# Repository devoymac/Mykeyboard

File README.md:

# Mykeyboard — Split Ergo Keyboard

Teclado ergonómico split de diseño propio. Proyecto de hardware abierto: esquemáticos y PCB en KiCad, firmware en QMK, y carcasa imprimible en 3D.

## Layout

Split columnar-stagger ISO-ES (español completo: Ñ, Ç, ‡, ¡, ¿), ~38 teclas por mitad, espacio dividido y flechas dedicadas.

## Estado

En desarrollo. Estructura del proyecto montada, KiCad 10.0.6 instalado, requisitos y layout definidos.

## Estructura del proyecto

```
Mykeyboard/
├── hardware/          # Diseño electrónico (KiCad)
│   ├── left/          # Mitad izquierda (esquemático + PCB)
│   ├── right/         # Mitad derecha (espejo de la izquierda)
│   └── shared/        # Librerías, símbolos, footprints y plantillas comunes
├── firmware/          # Firmware del teclado (QMK)
├── case/              # Carcasa imprimible en 3D (STL / FreeCAD)
├── docs/              # Documentación: requisitos, layout, BOM, decisiones
├── tools/             # Scripts de utilidad (generación, automatización)
└── README.md
```

## Hardware

- **KiCad**: 10.0.6 (esquemático y PCB).
- **Layout**: split columnar-stagger ISO-ES, ~37-38 teclas por mitad, placa única que se parte en dos (V-cut/mouse bites).
- **Controlador**: RP2040-Zero por mitad, conectadas por TRRS.
- **Switches**: Outemu Silent Lemon V3 (táctiles silenciosos), soldados.
- **Pantalla**: OLED 128x32 (I2C) en la mitad izquierda.
- **Extras**: encoder rotatorio EC11 (volumen/medios) en la mitad derecha.
- Ver [docs/requirements.md](docs/requirements.md), [docs/layout.md](docs/layout.md) y el [BOM](docs/bom.md).

## Firmware

QMK (cableado).

## Cómo contribuir / desarrollo

1. Clona el repositorio.
2. Abre los proyectos de KiCad en `hardware/left` y `hardware/right`.
3. Documenta cualquier cambio relevante en `docs/`.

## Licencia

Pendiente de decidir (recomendado: CERN-OHL-S para hardware, MIT para firmware).

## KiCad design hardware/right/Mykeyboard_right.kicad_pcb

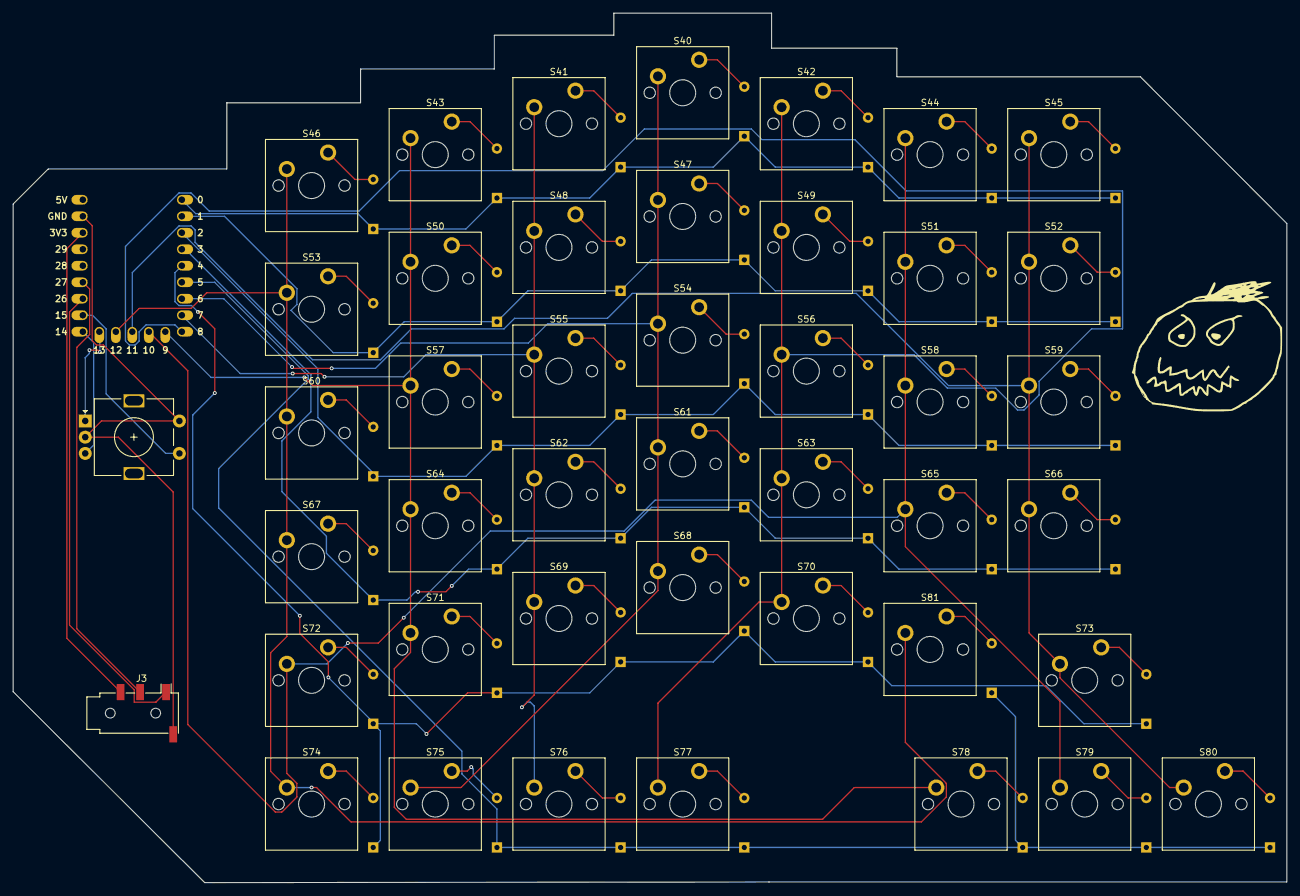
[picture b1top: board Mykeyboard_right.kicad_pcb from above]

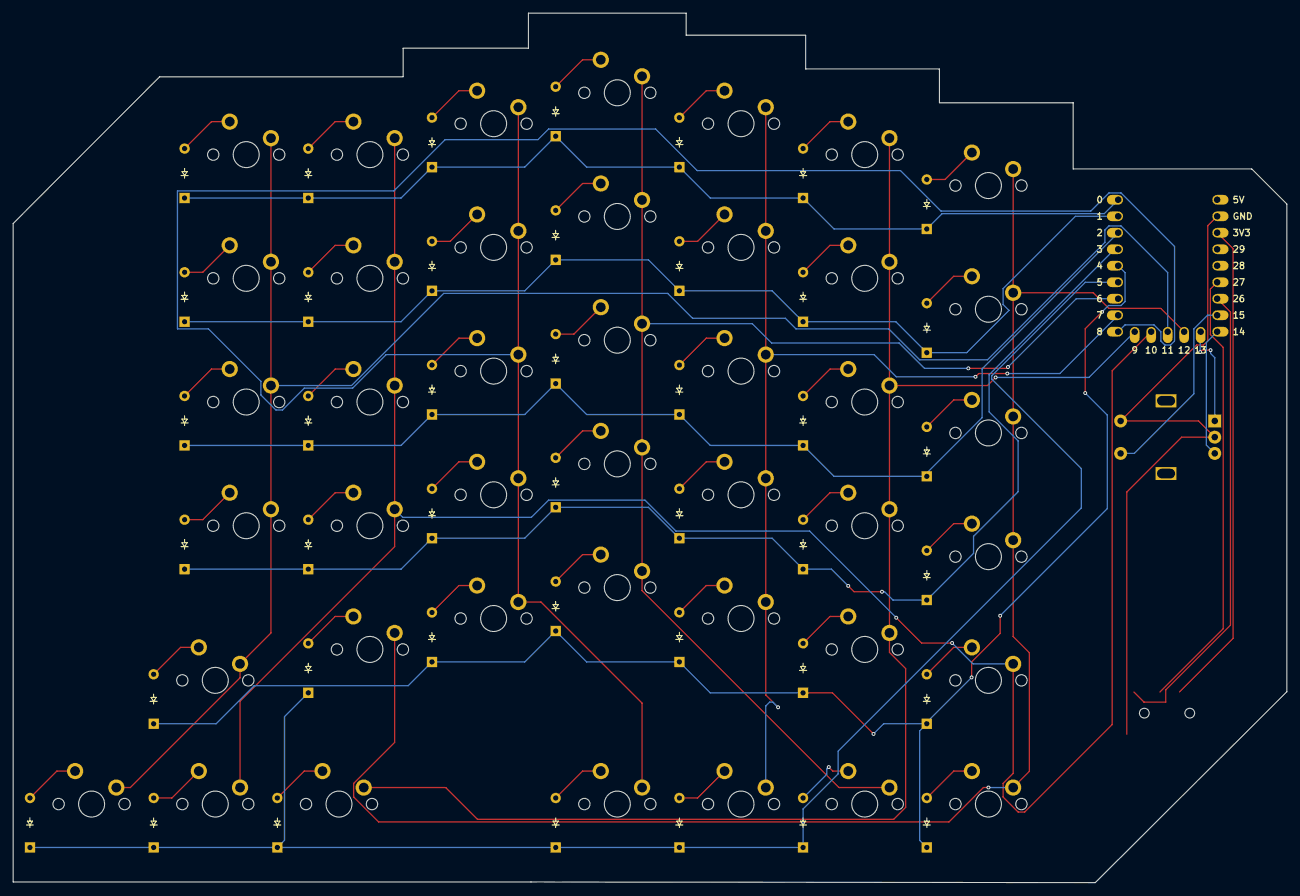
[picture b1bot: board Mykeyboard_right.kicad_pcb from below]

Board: 2 copper layers, 196.1 x 133.9 mm, 87 parts (42 on the bottom side), 62 nets.

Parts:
D40, D41, D42, D43, D44, D45, D46, D47, D48, D49, D50, D51, D52, D53, D54, D55, D56, D57, D58, D59, D60, D61, D62, D63, D64, D65, D66, D67, D68, D69, D70, D71, D72, D73, D74, D75, D76, D77, D78, D79, D80, D81: Diode_DO-35
J3: AudioJack4; Jack_3.5mm_PJ320D_Horizontal
S40, S41, S42, S43, S44, S45, S46, S47, S48, S49, S50, S51, S52, S53, S54, S55, S56, S57, S58, S59, S60, S61, S62, S63, S64, S65, S66, S67, S68, S69, S70, S71, S72, S73, S74, S75, S76, S77, S78, S79, S80, S81: MX_PCB_1.00u
SW1: RotaryEncoder_Switch; RotaryEncoder_Alps_EC11E-Switch_Vertical_H20mm
U2: RP2040_Zero

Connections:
/colum 7: S40.1, S47.1, S54.1, S61.1, S68.1, S75.1, U2.7 (6)
/colum 8: S41.1, S48.1, S55.1, S62.1, S69.1, S76.1, U2.8 (7)
/colum 9: S42.1, S49.1, S56.1, S63.1, S70.1, S77.1, U2.9 (8)
/colum 10: S43.1, S50.1, S57.1, S64.1, S71.1, S78.1, U2.10 (9)
/colum 11: S44.1, S51.1, S58.1, S65.1, S72.1, S79.1, U2.11 (10)
/colum 12: S45.1, S52.1, S59.1, S66.1, S73.1, S80.1, U2.12 (11)
/colum 13: S46.1, S53.1, S60.1, S67.1, S74.1, S81.1, U2.13 (12)
/row 6: D40.1 (K), D41.1 (K), D42.1 (K), D43.1 (K), D44.1 (K), D45.1 (K), D46.1 (K), U2.1 (0)
/row 7: D47.1 (K), D48.1 (K), D49.1 (K), D50.1 (K), D51.1 (K), D52.1 (K), D53.1 (K), U2.2 (1)
/row 8: D54.1 (K), D55.1 (K), D56.1 (K), D57.1 (K), D58.1 (K), D59.1 (K), D60.1 (K), U2.3 (2)
/row 9: D61.1 (K), D62.1 (K), D63.1 (K), D64.1 (K), D65.1 (K), D66.1 (K), D67.1 (K), U2.4 (3)
/row 10: D68.1 (K), D69.1 (K), D70.1 (K), D71.1 (K), D72.1 (K), D73.1 (K), D74.1 (K), U2.5 (4)
/row 11: D75.1 (K), D76.1 (K), D77.1 (K), D78.1 (K), D79.1 (K), D80.1 (K), D81.1 (K), U2.6 (5)
unnamed: D40.2 (A), S40.2
unnamed: D41.2 (A), S41.2
unnamed: D42.2 (A), S42.2
unnamed: D43.2 (A), S43.2
unnamed: D44.2 (A), S44.2
unnamed: D45.2 (A), S45.2
unnamed: D46.2 (A), S46.2
unnamed: D47.2 (A), S47.2
unnamed: D48.2 (A), S48.2
unnamed: D49.2 (A), S49.2
unnamed: D50.2 (A), S50.2
unnamed: D51.2 (A), S51.2
unnamed: D52.2 (A), S52.2
unnamed: D53.2 (A), S53.2
unnamed: D54.2 (A), S54.2
unnamed: D55.2 (A), S55.2
unnamed: D56.2 (A), S56.2
unnamed: D57.2 (A), S57.2
unnamed: D58.2 (A), S58.2
unnamed: D59.2 (A), S59.2
unnamed: D60.2 (A), S60.2
unnamed: D61.2 (A), S61.2
unnamed: D62.2 (A), S62.2
unnamed: D63.2 (A), S63.2
unnamed: D64.2 (A), S64.2
unnamed: D65.2 (A), S65.2
unnamed: D66.2 (A), S66.2
unnamed: D67.2 (A), S67.2
unnamed: D68.2 (A), S68.2
unnamed: D69.2 (A), S69.2
unnamed: D70.2 (A), S70.2
unnamed: D71.2 (A), S71.2
unnamed: D72.2 (A), S72.2
unnamed: D73.2 (A), S73.2
unnamed: D74.2 (A), S74.2
unnamed: D75.2 (A), S75.2
unnamed: D76.2 (A), S76.2
unnamed: D77.2 (A), S77.2
unnamed: D78.2 (A), S78.2
unnamed: D79.2 (A), S79.2
unnamed: D80.2 (A), S80.2
unnamed: D81.2 (A), S81.2
unnamed: J3.R2, U2.21 (3V3)
unnamed: SW1.A, U2.14 (13)
unnamed: SW1.B, U2.15 (14)
unnamed: SW1.S1, U2.16 (15)
unnamed: J3.T, U2.17 (26)
unnamed: J3.R1, U2.18 (27)
unnamed: J3.S, SW1.C, SW1.S2, U2.22 (GND)
